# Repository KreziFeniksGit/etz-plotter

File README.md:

# ETZ plotter v2: whole device

**Open in FreeCAD:** `out/ETZ_plotter_parked.FCStd` (native, coloured, grouped) or `out/ETZ_plotter_parked.step`.
`ETZ_plotter_working.*` is the same model at Y 250, X 400, magnet face 5 mm, wrist 90 deg.
Tree: ETZ_plotter > Base_and_Y_axis, Y_carriage_and_X_axis, Wrist_module, Electronics_and_controls, Cables_and_chains, Fasteners, Field_reference.
Coordinates: X along the 600 mm side of the polygon, Y along the 500 mm side, Z up from the table (mm).

**Print files:** `out/printed/` has all 24 printed designs (15 frame parts + 9 wrist module parts) in print orientation, as STEP (PrusaSlicer, OrcaSlicer, Bambu Studio and Cura 5.x open STEP).
`y_beam_riser_x4` is printed four times.

**Wiring:** `wiring.md` (power, stop button, ESP32-S3 pins, every harness, driver currents).

**Tolerance tests:** `tolerance/` has 11 test coupons (STEP) and `tolerance/README.md` says how to test each one and which
constant to change. Print them before the real parts.

## Plywood, bolts and feet (v2.14)
- **Plywood DXF:** `out/plywood_base.dxf` (1:1, mm, origin = the board's -x/-y corner, seen from the top): outline + 18 through
  holes only (the shop cannot do depths). Hole list: `out/plywood_base_holes.csv`. Feet sit flat under the board; beam bolts M5x22.
- No wood screws: bolts through the plywood with a washer and hex nut underneath. Printed PETG feet (`foot_x4`) with an insert.
- The control board, panel, breadboard and battery are not in the model: place and drill them where you want.
- Control PCB: `pcb/README.md`.

## Stack-height sensor (v2.11)
- **TOF400C (VL53L1X)** under the wrist shelf at x 125.5, looking down, on 2 posts with M2 self-tapping screws.

## Camera (v2.16)
- **DF-1901A** board (54 x 19, lens d 14 x 23 in the middle, 3 M3 holes) sits ON TOP of the wrist shelf at x 150,
  along y, lens down through a 15 mm hole, on 3 nylon spacers 4.2x7x3 with 3x M3x12 + nut. Under the shelf the long lens
  would hit a 5-stack; on top its lowest point is 30 mm at face height 5. The single hole sits on a shelf tab at y -18..-3.
  It counts the checkers in a stack, reading with the magnet up (49..74 mm). Wiring and firmware notes: `wiring.md`.
  (An RDS3235 servo was tried and dropped, 16 Oct: the wrist stays on the MG996R.)

## Assembly simulation and 6 mm plywood (v2.9)
`tools/assembly_sim.py` builds the device in order (`docs/print_test_order.md`, "Order that matters") and checks that every
part can slide into place, every screw head can get in, a hex key or screwdriver reaches it, nuts can be held, T-nut slots are
still open and the soldering iron reaches every insert (`out/assembly_sim.json`: 0 problems). It found six places a person
could not assemble, now fixed:
- **Y carriage:** the 4 block screw heads were partly under the post socket walls: vertical notches through the walls (y walls 6 mm).
- **X motor mount:** two motor screw heads hit the cheeks: grooves in the cheeks.
- **Wrist carriage:** two block screw heads were under the servo plate: a notch for one; the other hole is dropped (3 screws on the X block).
- **Servo tabs:** the nylocs could not be held (servo case, boom): M2x8 self-tapping screws into the servo plate instead.
- **Magnet:** its screw head could not pass the 5 mm shaft bore: an M3x8 set screw in a Ruthex insert in the hub, magnet spun on (Loctite 243).
- **Control panel:** no room for a driver at the connector board screws: two 6 x 6 access windows in the +x wall.
**6 mm plywood** (Egor's board): 20 x 10 rubber feet in 1 mm recesses keep the plywood top at z 15, so nothing above moved;
beam bolt heads sunk 2 mm; all wood screws shortened so they bite 4..6 mm and none comes out underneath.

## V-slot frame and NEMA17 pancake wrist (v2.8)
- **2020 V-slot** everywhere (Y beam 400, post 130, boom 270): OpenBuilds section, 6 mm slot opening with the V-groove. The drop-in
  T-nuts, beam riser tongues, rails, socket and Soberizavod slot-6 cast brackets (T01) all still fit; the fastener check passes.
- **Wrist stepper = NEMA17 pancake 17HS4023S** (42 x 42 x 23, 0.7 A, ~13 N cm, 0.14 kg), on 4x M3x8 from under the shelf.
  To clear the lower arm and the end plate, the magnet axis moved +5 mm in X (to 110 from the servo axis) and -2.5 mm in Y,
  so **X travel is now pivot X 287..430** (the magnet still reaches X 397..540). The camera moved to x 147 and screws on from below.
  Picture: `out/render_wrist_nema17_pancake.png`.
- Servo lift: 0.23 N m needed with the heavier motor = 21 % of the MG996R's stall torque at 6 V.

## Stiffness, backlash and open belts (v2.7)
`docs/stiffness_review.md` has the whole review. FEA of the load-carrying printed parts (`tools/fea.py` -> `out/fea.json`,
gmsh + CalculiX from FreeCAD): every part now moves its pulley or idler <= 0.04 mm and tilts it <= 0.11 deg under 50 N of belt pull.
- **x_motor_mount:** 6 mm plate, top and bottom flanges, each arm also bolted (M5) to the post's -x face: pulley tilt 0.20 -> 0.025 deg.
- **y_motor_mount:** 6 mm plate, base on both sides, 4 gussets, 4 fixed wood screws (no tension slots any more).
- **x_idler_bracket** (the weakest part, 0.65 deg tilt -> 0.11): 12 mm end cap, a channel round an `x_idler_slider` pushed by an M3 screw in line with the axle.
- **y_idler_bracket:** axle slot + `y_idler_slider` pushed by an M3 screw in a lug (3 mm travel).
- **Open belts:** both ends clamp on the carriage (Y clamp 30 mm long with 3 screws, X clamp 42 mm with 3 screws), 6-9 teeth per end.
  Tension is set at the idler sliders; the motors never move.
- Backlash budget: 0.11 mm (Y) and 0.07 mm (X) on reversal (belt stretch, stepper, mounts, tooth clearance) against the 10 mm tolerance.
- Print the load parts with 6 walls and >= 50 % infill.

## Fasteners (v2.2)
All 140 fasteners are in the model (`Fasteners` in the tree): every screw with its head, nut, washer, heat-set insert or T-nut,
341 solids. `out/fastener_bom.csv` is the complete list with quantities. The check (`assembly.py`) found and fixed these:
- **Rubber feet:** a 3 mm foot cannot hold a screw. Now screw-on feet 20 x 7 mm sit 4 mm deep in pockets under the plywood
  (20 mm Forstner bit) and stick out 3 mm, so nothing else moves. Wood screw 3.5x12 from below.
- **Y beam bolts:** a flush M5 countersunk screw was either too short for the T-nut or hit the profile core. Now M5x20 socket caps
  in 9.3 mm counterbores, 7.5 deep, from below.
- **Y idler moved to y 12** (was 22): its axle nut hit the Y block when parked. The beam end plate of the idler bracket is lower
  (z 41.5) to clear the same nut.
- **X idler axle:** the nut would have hit the boom, so the bolt head now sits between the boom and the idler and the nut is outside.
- **Corner brackets:** the centre rib was in the way of the screw heads; modelled with side walls and holes 11 mm from the corner
  (VERIFY on your brackets). The two heads on one bracket touched at 10 mm.
- **Rails:** MGN12 rails now have their counterbored M3 holes (25 mm pitch; VERIFY), M3x8 into T-nuts.
- **Servo tab nuts:** the wrist carriage ribs were cut to 7 mm so the washers and nylocs fit.
- **Trays:** screw heads hit the breadboard and battery tray walls; ears moved out 2.5 / 1.5 mm, the breadboard 2 mm further +Y.
- **Y chain moving end:** button heads (M3x20) so the cable bundle fits over them.
Results: no fastener clips any part at rest or in 16 poses against the moving parts; every screw engages enough
(inserts >= 4 mm, T-nuts >= 2.5..3 mm, nuts fully, tapped metal within its thread depth) and blind screws end inside their target.

## Cable chains and cables (v2.1)
- **X chain** (10 x 15 R18, 297.5 mm = 17 links since v2.17, was 280): fixed end on the boom top at x 230..250 (2 M3 drop-in T-nuts), lower run lies on the boom,
  U-bend toward +X, upper run back to the moving end on top of `chain_post`. The post top is now at z 208 (boom top 172 + 2 x R18)
  and has a 45 deg brace and a slot for the end link screws (any hole spacing fits).
- **Y chain** (10 x 15 R18, 250 mm): lower run in the printed `y_chain_guide` on the plywood (x 235.5, y 213..421), U-bend toward +Y,
  upper run to the moving end on top of the Y carriage (M3 + nut through a slot). The guide's 17 mm floor (pockets underneath)
  lifts the chain so the upper run meets the carriage top.
- Both chains are rebuilt for every pose: the bend sits where the chain length puts it (it moves at half the carriage speed).
  X bend x 401..484 (v2.17), Y bend y 250..418: the Y bend stays 57 mm inside the polygon edge.
- **Cable tunnel:** the Y beam now sits on four printed risers (10 mm), so the cables from the battery, the panel and the Y motor
  cross under the beam (at y 60 and y 205) to the electronics board. Before this, nothing could reach the board without crossing the
  Y carriage's path. The post is 10 mm shorter (130 mm), so the boom height is unchanged.
- The cable bundles are modelled as tubes (`cable_*`), so the collision check sees them.
- **X travel was pivot X 292..435** (v2.2; 287..430 since v2.8; **287..452 since v2.17**, see below) (magnet X 397..540, the cells need 397..537). Raising the Y axis left the
  wrist carriage 3 mm into the Y carriage at the old minimum (256).

## Whole-device check (`assembly.py`, results in `out/assembly_review.json`)
- no clash between any two parts at rest, and no cable passes through a part;
- no collision in 54 poses: Y 40/124/208/292/376 x X 287/328/369.5/411/452 x face height 5/40 mm, plus wrist +-90/180, chains and cables included;
- parked device inside the 600 x 500 polygon and zones 1+2, feet only in zone 1; during the run parts may leave the polygon (ETZ rules): at PXB 452 the wrist shelf passes 7 mm beyond the 600 mm edge;
- lowest part over the field at face height 5 mm: camera lens at 30 mm (clears a 5-stack);
- every printed part: walls >= 2.4 mm, no unrounded internal corner, no overhang > 45 deg, widest bridge 9.3 mm, fits 220 x 220.

## Stability and stiffness (`tools/stability.py`, results in `out/stability.json`)
- Mass about 4.1 kg with all screws (base 2.61, Y carriage and boom 1.03, wrist module 0.42, chains 0.08; v2.7).
- Tipping: the centre of mass stays at least 92 mm inside the feet. Tipping would need 31 m/s2 (3.2 g); the design acceleration is 2 m/s2.
- Rail loads: worst moment 1.65 N m on the Y block against 37.5 N m rated (23x margin).
- Sag of the magnet from the aluminium profiles: at most 0.16 mm. The printed socket and the corner brackets add more; calibration takes it out,
  and the placement tolerance is 10 mm.

**Regenerate:** `freecad export_gui.py` (needs the FreeCAD GUI for colours), `./fcpy assembly.py` and `./fcpy tools/stability.py`
with FreeCAD's python. `./fcpy tools/render_pose.py Y X h wrist out.png` renders any pose.

**Frame parts (same rules as the wrist module):** y_carriage (post socket with round relief groove, block screws sunk 5 mm: fit them
before the post; slot for the Y chain end), y_belt_spacer, y_belt_clamp (two belt ends, tooth grooves), y_motor_mount (fixed, gusseted), y_idler_bracket
(idler slot, tension lug, Y home switch post), y_idler_slider, y_beam_riser x4 (tongues locate the beam in its slot), y_chain_guide, x_motor_mount (M5 into the post's +y and -x faces,
X home switch), x_idler_bracket (slotted axle, tension lug), x_idler_slider, post_cap, foot_x4. The control panel and the battery / breadboard trays are no longer printed
(v2.14: Egor places the electronics on the plywood by hand).

**Screws:** `out/fastener_bom.csv` is the complete list (it replaces the screw lists further down where they differ). Zip ties are not modelled.

---

# ETZ plotter v2: component choices and the wrist module

Model v2 follows the design rules: parameters at the top of the script, separate printable parts, rule tolerances, 2.4 mm minimum walls, filleted corners, at most 45 degree overhangs, short bridges, cable-tie features. The CAD is FreeCAD (OpenCascade) Python, so the solids are real B-rep with true fillets.

## Files
- `wrist/wrist_module.py`: the parametric model (all dimensions in sections 1 to 3 at the top).
- `wrist/review.py`: the review that produced the numbers below.
- `wrist/out/*.step`: the wrist parts in print orientation (the same files are in `out/printed/`). `wrist/out/wrist_module_assembly.step`: the whole module with the bought parts.
- `wrist/out/review.json`: all review results. `wrist/out/*.png`: renders.
- `components.csv`: every component of the device, with the reason it was chosen and the data used in the CAD.
- `vendor/`: real models of bought parts (MG996R, 25T aluminium arm horn, 17HS16-2004S1; 11HS12-0674S is no longer used; no model of the 17HS4023S pancake yet; the 684 bearing and MGN12 meshes are kept for reference only). The exported STEP/FCStd use them; the fast checks use simple shapes sized from them, and `assembly.py` also re-checks with the real models (`detailed_*` results).

Run the model yourself: install FreeCAD 1.0 or 1.1 (Linux AppImage or Windows installer), then
`freecadcmd -c "exec(open('wrist_module.py').read())"`, or open the file in the FreeCAD GUI with Macro > Macros > Execute.

## Wrist module: design decisions
- **Carriage and servo plate are one L-part.** This gives a stiff joint with no screws. It prints with the block face down; the servo window has a W-shaped 45 degree roof, so it needs no bridge. The lower pivot boss is a teardrop for the same reason.
- **Parallelogram, 80 mm arms.** The magnet face stays level from 5 to 40 mm. The servo swings +-12.6 degrees and the X shift (up to 1.9 mm) is corrected in software.
- **Bearings in the arms, clamped on the inner ring only.** A nylon spacer 4.2 x 7 x 3 goes through a 7.6 mm shoulder hole on one side and a 7 mm shim washer goes on the other, so nothing touches the outer ring. Moving gaps are 0.5 to 0.8 mm.
- **The top arm bolts to a 25T aluminium single-arm horn**: centre screw into the spline plus one M3 into the horn's tapped hole at r 24, with the horn's arm lying along the top arm.
- **Lightening slots** in both arms remove about 25 % of the web. The two flanges carry the bending, so stiffness hardly drops.
- **Shelf and end plate are separate flat parts.** Both print flat, so the stepper and pivot holes are vertical, round and accurate. They join with two M3 screws into inserts in the end plate's foot pad, which sits clear of the pivot nut.
- **The belt clamp** has half-round grooves at 2 mm pitch that take the belt teeth; it holds both ends of the open X belt (42 mm, 3 screws).
- **No wrist home sensor** (Egor, 12 Oct): the hall switch and the hub's flag magnet were removed. Set the wrist to its mark by hand before power-up; the firmware counts the angle from there.
- **MG996R servo**: M2 bolts with large washers through its 4.5 mm tab holes (M3 would leave only 2 mm of plastic to the window); shallow grooves take the ribs under its tabs.

## Tolerances used
| Feature | Size |
|---|---|
| M3 / M4 clearance holes | 3.25 / 4.25 (+0.25); camera M2 self-tapping pilots 1.8 |
| Wrist NEMA17 pancake screw holes, pilot | 3.2, 22.2 (+0.2) |
| 684ZZ press seat | 9.12 (+0.12) |
| D-bore on the stepper shaft | 5.12 with flat at 4.62 (+0.12) |
| Servo window | case +0.4 per side |
| Spacer in the shoulder hole | 0.3 radial |
| Heat-set insert hole | 4.0 x 6.5 deep |

## Review results
- Interference: none, checked at face height 5, 10, 16, 22.5, 30, 36 and 40 mm and wrist angle 0, 90 and 180 degrees, with every bought part included.
- Smallest moving gaps: 0.3 mm (spacers in the arms) and 0.5 mm (lower arm to its boss and to the shelf). Servo case to window: 0.36 mm.
- Lowest point at face height 5 mm: camera lens 30 mm, which clears a stack of 5 checkers (25 mm).
- Every printed part: walls at least 2.4 mm, no unrounded internal corner, no overhang beyond 45 degrees, widest bridge 6.3 mm, all fit a 220 x 220 bed. About 72 g of PETG.

## Wrist module parts list
| Part | Qty | Print orientation |
|---|---|---|
| wrist_carriage | 1 | block face down |
| x_belt_riser | 1 | standing |
| x_belt_clamp | 1 | grooves up |
| chain_post | 1 | on its -Y face |
| arm_top, arm_bottom | 1 + 1 | flat |
| end_plate | 1 | -Y face down |
| shelf | 1 | stepper face down |
| wrist_hub | 1 | shaft end down |

Suggested settings: PETG, 0.2 mm layers, 4 walls, 40 % gyroid, no supports.

**Bought parts:** MG996R servo + 25T aluminium arm horn, NEMA17 pancake 17HS4023S, P20/15 5 V magnet, 3x 684ZZ, 6x nylon spacer 4.2x7x3 (3 pivots, 3 camera), 3x shim 4.2x7x0.8, camera DF-1901A, 10x Ruthex M3x5.7.

**Screws:**
- 4x M3x6 ISO4762: carriage to the rail block.
- 4x M2x12 ISO4762 + DIN 9021 washer under the head + nyloc (no washer under the nut): servo tabs.
- 1x M4x30 ISO4762 + nyloc: lower A pivot.
- 2x M4x20 ISO4762 + washer + nyloc: B pivots.
- 2x M3x10: belt riser. 2x M3x10: chain post. 2x M3x8: belt clamp. 2x M3x12 + nut: X chain end on the post.
- 2x M3x10: shelf to end plate.
- 4x M3x8 ISO7380: wrist NEMA17 pancake, from below the shelf.
- 3x M3x12 ISO4762 + hex nut: camera board, from the top through the board, a nylon spacer and the shelf, nut below.
- 1x M3x6 or M3x8 ISO7380: magnet. Use the length that suits the magnet's thread depth.
- 1x M3x10 ISO7380: top arm to the horn (r 24 hole, tapped M3 in the horn: VERIFY).

## Assembly order
1. Press the heat-set inserts: riser (2 top, 2 bottom), chain post foot (2), end plate foot (2).
2. Screw the wrist carriage to the rail block (4x M3x6 from below). Do this before the servo goes in: the servo covers two of the screws.
3. Fit the riser and chain post from below (M3x10).
4. Push the servo through the window from the -Y side and bolt the tabs (M2x12, large washer under the head, nyloc).
5. Press the bearings into both arms from the end-plate side (flush).
6. Set the servo to its centre pulse (1500 us), fit the horn with the arm level, and screw the top arm to it.
7. Lower pivot A: M4x30 from the servo side, through the boss, spacer, bearing, shim and nyloc. Snug only: the arm must swing freely.
8. Screw the shelf to the end plate (2x M3x10 from below). Mount the NEMA17 pancake (4x M3x8 from below, connector toward +x, away from the end plate) and the camera on top (3x M3x12 down through board + spacer + shelf, nuts below).
9. B pivots: M4x20 with washer and spacer from the arm side, then bearing, shim, end plate and nyloc.
10. Press the hub onto the stepper shaft (D flat aligned), with the magnet screw already inside it, then screw on the electromagnet.
11. Route the cables (see wiring.md): the harness tie on the end plate, two ties round the top arm, servo lead to the bundle, two ties on the chain post.

## Measure before printing (marked VERIFY in the script)
Wrist stepper 17HS4023S: body height (23), shaft length (20..24; the hub takes up to 23), screw thread depth (4.5), which side the connector is on. Servo (MG996R, taken from a third-party STEP model): tab face to cover top, case height, spline centre to case end, tab hole spacing (48.4), horn face height, horn screw hole thread. Magnet: thread depth. Enter the measured values at the top of `wrist_module.py`; everything else follows.

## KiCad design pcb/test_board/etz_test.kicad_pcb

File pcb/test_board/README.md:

# ETZ control: TEST BOARD T1 (2-layer, JLCPCB), 9 Nov 2026

This is a test version of `../etz_control.kicad_sch`, built as a factory 2-layer board. **The originals are untouched.** Everything lives in this folder.

> **Do not order T1 yet (pin audit, 10 Nov 2026).** `etz_control.kicad_sch` still has the *old* single-board pin map (22 Oct). The split boards and firmware v5 use the new one (`wiring.md` section 2, `firmware/include/pins.h`). On T1 every STEP/DIR pin, the TMC UART (15/16 instead of 5/6), I2C, the home switches, start, the LED, the magnet and the servo are on different GPIOs. Driver EN sits on GPIO13 with a pull-up, so the drivers stay off. The UART addresses are 0/1/2/3 instead of X 0, Y 2, wrist 3. Next step: rebuild T1 with the `pins.h` map.

| File | What it is |
|---|---|
| `test_parts.py` | Parts table: a copy of the one in `build_pcb.py`, plus the fixes below |
| `test_sch.py` → `etz_test.kicad_sch`, `etz_test_schematic.pdf` | The fixed schematic (ERC 0, netlist identical to the parts table) |
| `layout.py` → `etz_test.kicad_pcb` | The board, made from the schematic's netlist; footprints are linked to the symbols, so "Update PCB from Schematic" works |
| `nl.py`, `probe.py` | Netlist reader and a footprint-size helper |
| `renders/` | Top and bottom pictures |

To rebuild:
```
"C:\Program Files\KiCad\10.0\bin\python.exe" test_sch.py
"C:\Program Files\KiCad\10.0\bin\python.exe" layout.py 30
```

## Fixes compared to etz_control v1.0, and why

1. **XT30 polarity (J11).** The KiCad AMASS footprint has pad 1 = minus and pad 2 = plus. v1.0 had them swapped, so the drive battery would have reversed VM on all four TMC2209s, which kills them.
2. **TVS diodes D3 and D4 (SMBJ18A) at both power inputs.** They clamp spikes when a plug goes in and when motors brake. 4S LiPo is 16.8 V max, so an 18 V stand-off does not conduct in normal use. If the battery is plugged in backwards, the TVS shorts it and the battery fuse blows, and nothing else gets reverse voltage. VERIFY: the clamp is ~29 V and the TMC2209 VM absolute maximum is 29 V, which leaves no margin. SMBJ16A (clamp ~26 V) is the safer choice if 4S never goes above 16.8 V (stand-off 16 V, so it leaks a little at full charge).
3. **100 nF ceramic C9–C12 at every driver VM pin.** The 100 µF electrolytic is too slow for the chopper's fast current edges. The small cap sits on the VM and GND pins.
4. **4.7 µF ceramic C13 and C14 at each Mini560 input.** A buck draws its input current in sharp pulses. A ceramic cap right at the input keeps that loop small, which means less noise.
5. **ADC filter caps C15 (VBAT_SENSE) and C16 (STOP_SENSE),** like C8 already does on A_IO. A divider with a cap gives the ADC a low-impedance source.
6. **Test points TP5 VBAT, TP6 VDRIVE, TP7 GND,** so the meter probe has a place to go.

## Layout decisions

- **Zones:** power on the right edge (XT60 + XT30 face out, TVS on their pins, then both bucks). Drivers along the top, each with its motor plug straight above its motor pins. ESP32 bottom-left with the USB end at the left edge. All small plugs along the bottom.
- **Drivers in pin order:** W, Y, X, spare left to right, which is the order of their STEP/DIR pins on the ESP32. Signals run straight down with no crossings.
- **Power first:** VBAT, VDRIVE, the 5 V rails, the motor phases and 3V3 are routed first, at widths chosen by current (1.5 / 1.0 / 0.8 / 0.5 mm). Signals are routed afterwards, around them.
- **Ground:** no ground traces. Every SMD ground pad gets its own via into the pours. Both layers are GND pours, tied with stitching vias. The bottom layer is kept as clean as possible so the return currents have a solid path.
- **Labels:** each plug's name is on the silkscreen (X, Y, TOF, PANEL...), with + and − at the battery plugs. The revision is also etched in copper, so a bare board can still be identified.

## Left open (VERIFY / next revision)

- **GPIO38 (TOF_XSHUT).** On DevKitC-1 v1.1 the RGB LED is on IO38, and nothing can be moved: every allowed GPIO is already in use, and 3, 45, 46 and 48 are forbidden by the README. It works on v1.0. On v1.1 the LED will flicker with XSHUT. Check which DevKit version is in the box.
- **No ESD protection on J17 (panel cable).** It goes off-board, so it is the most likely place for a zap. Next revision: a TVS array.
- **No 22 Ω series resistors on the STEP lines.** They would soften edge ringing on long traces. Not needed at these lengths.
- **The spare driver U7 has no STEP/DIR.** All GPIOs are used. It only gets its power, plug and UART address.
- **Reverse polarity is handled by TVS + fuse (crowbar).** A P-FET would be nicer (no blown fuse), but at 4S the gate needs a zener clamp. See pcb-brain "P-MOSFET power path".

## Checks run (10 Nov 2026)

- Schematic: ERC 0. The netlist is identical to the parts table (77 parts, 58 nets).
- Board 146 x 100 mm, 2 layers. 580 tracks + vias, 25 ground vias at SMD pads, 193 stitching vias.
- DRC (`kicad-cli pcb drc --schematic-parity`): **0 errors, 0 unconnected, 0 schematic-parity issues**. One silkscreen-overlap warning (C13 reference touches the XT60 outline; cosmetic).
- Power width: the routes have their class width. Short neck-downs happen only where a track enters 2.54 mm-pitch module pins. The longest is about 10 mm at 1.125 mm, still ~3 A (VERIFY against the real current draw).
- 5 GND header pins (J9.2, U1.23, U3.3, U3.16, U4.16) had their thermal spokes blocked by passing tracks, so they connect solid to the pour. These are 0.64 mm pins, still easy to solder.
- Teardrops: the KiCad 10 Python API didn't expose them. Add them in the GUI if you want (Edit → Edit Teardrops).
- `gerbers/` contains the Gerber + drill files for JLCPCB. **Before ordering, open the board in KiCad, look it over yourself, and zip the gerbers.**

## How the routing works (lessons used)

1. Pass 1: only power, motor and 3V3 nets are visible to Freerouting. They get the best paths and the widest tracks.
2. The power tracks are locked. Pass 2 routes signals around them.
3. GND is never routed as tracks. Each SMD ground pad has its own via, and both layers are GND pour.
4. Bug found and fixed: at first the vias were netless, and Freerouting took them for other nets (shorts to GND). Giving them GND from the start stopped that.

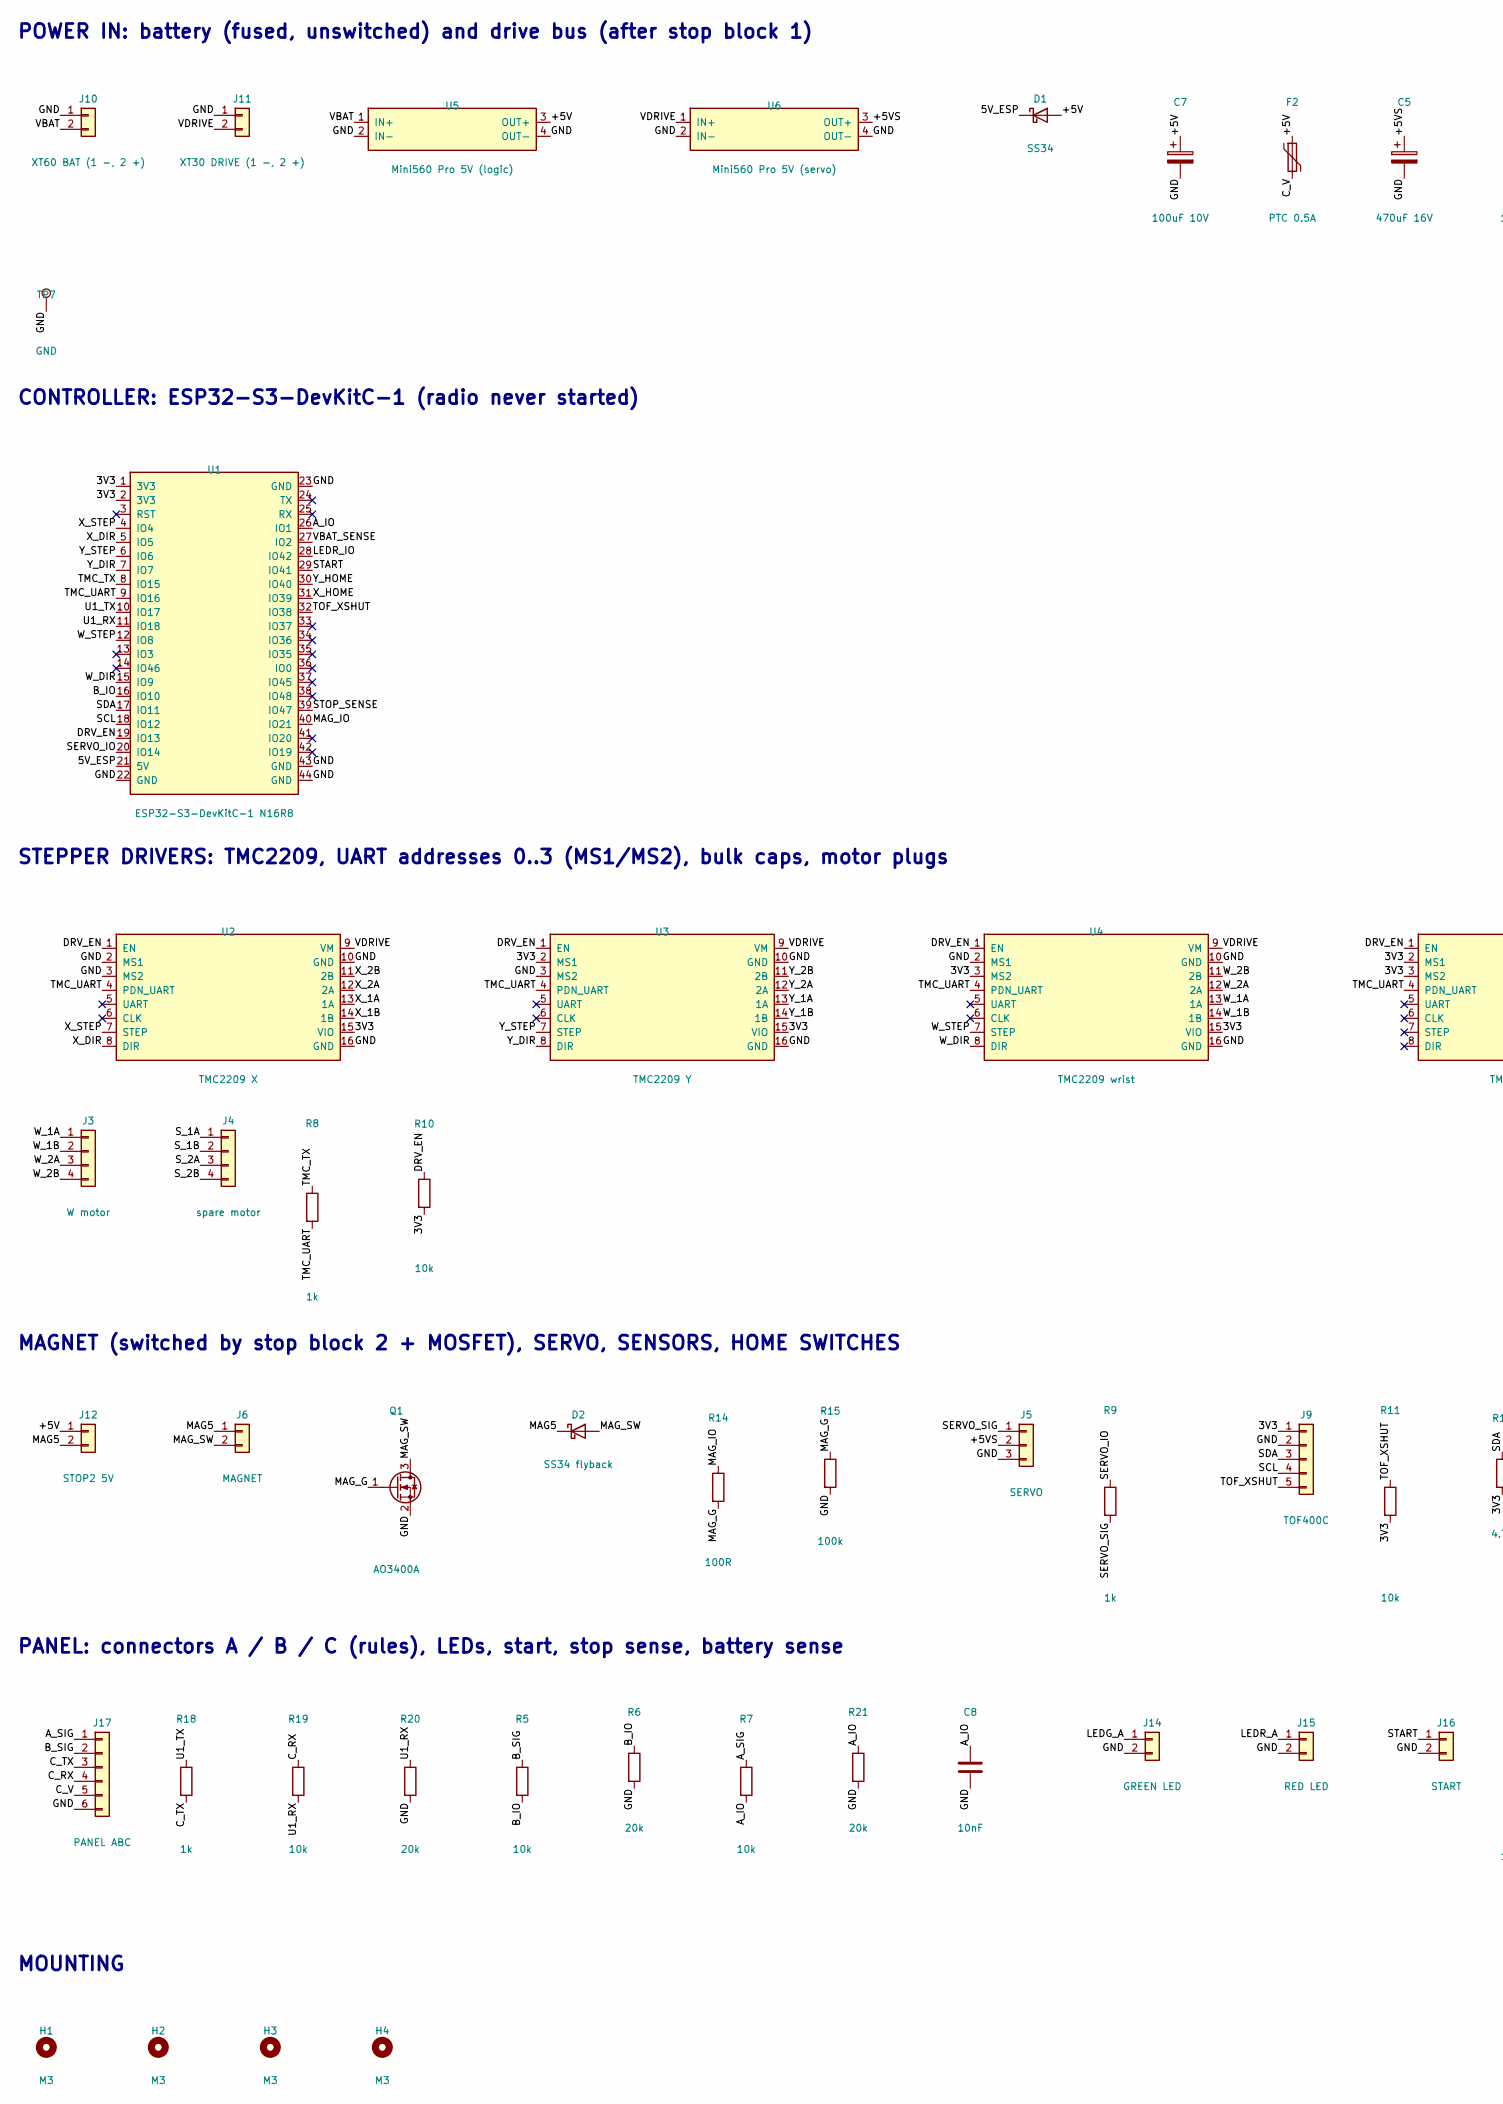
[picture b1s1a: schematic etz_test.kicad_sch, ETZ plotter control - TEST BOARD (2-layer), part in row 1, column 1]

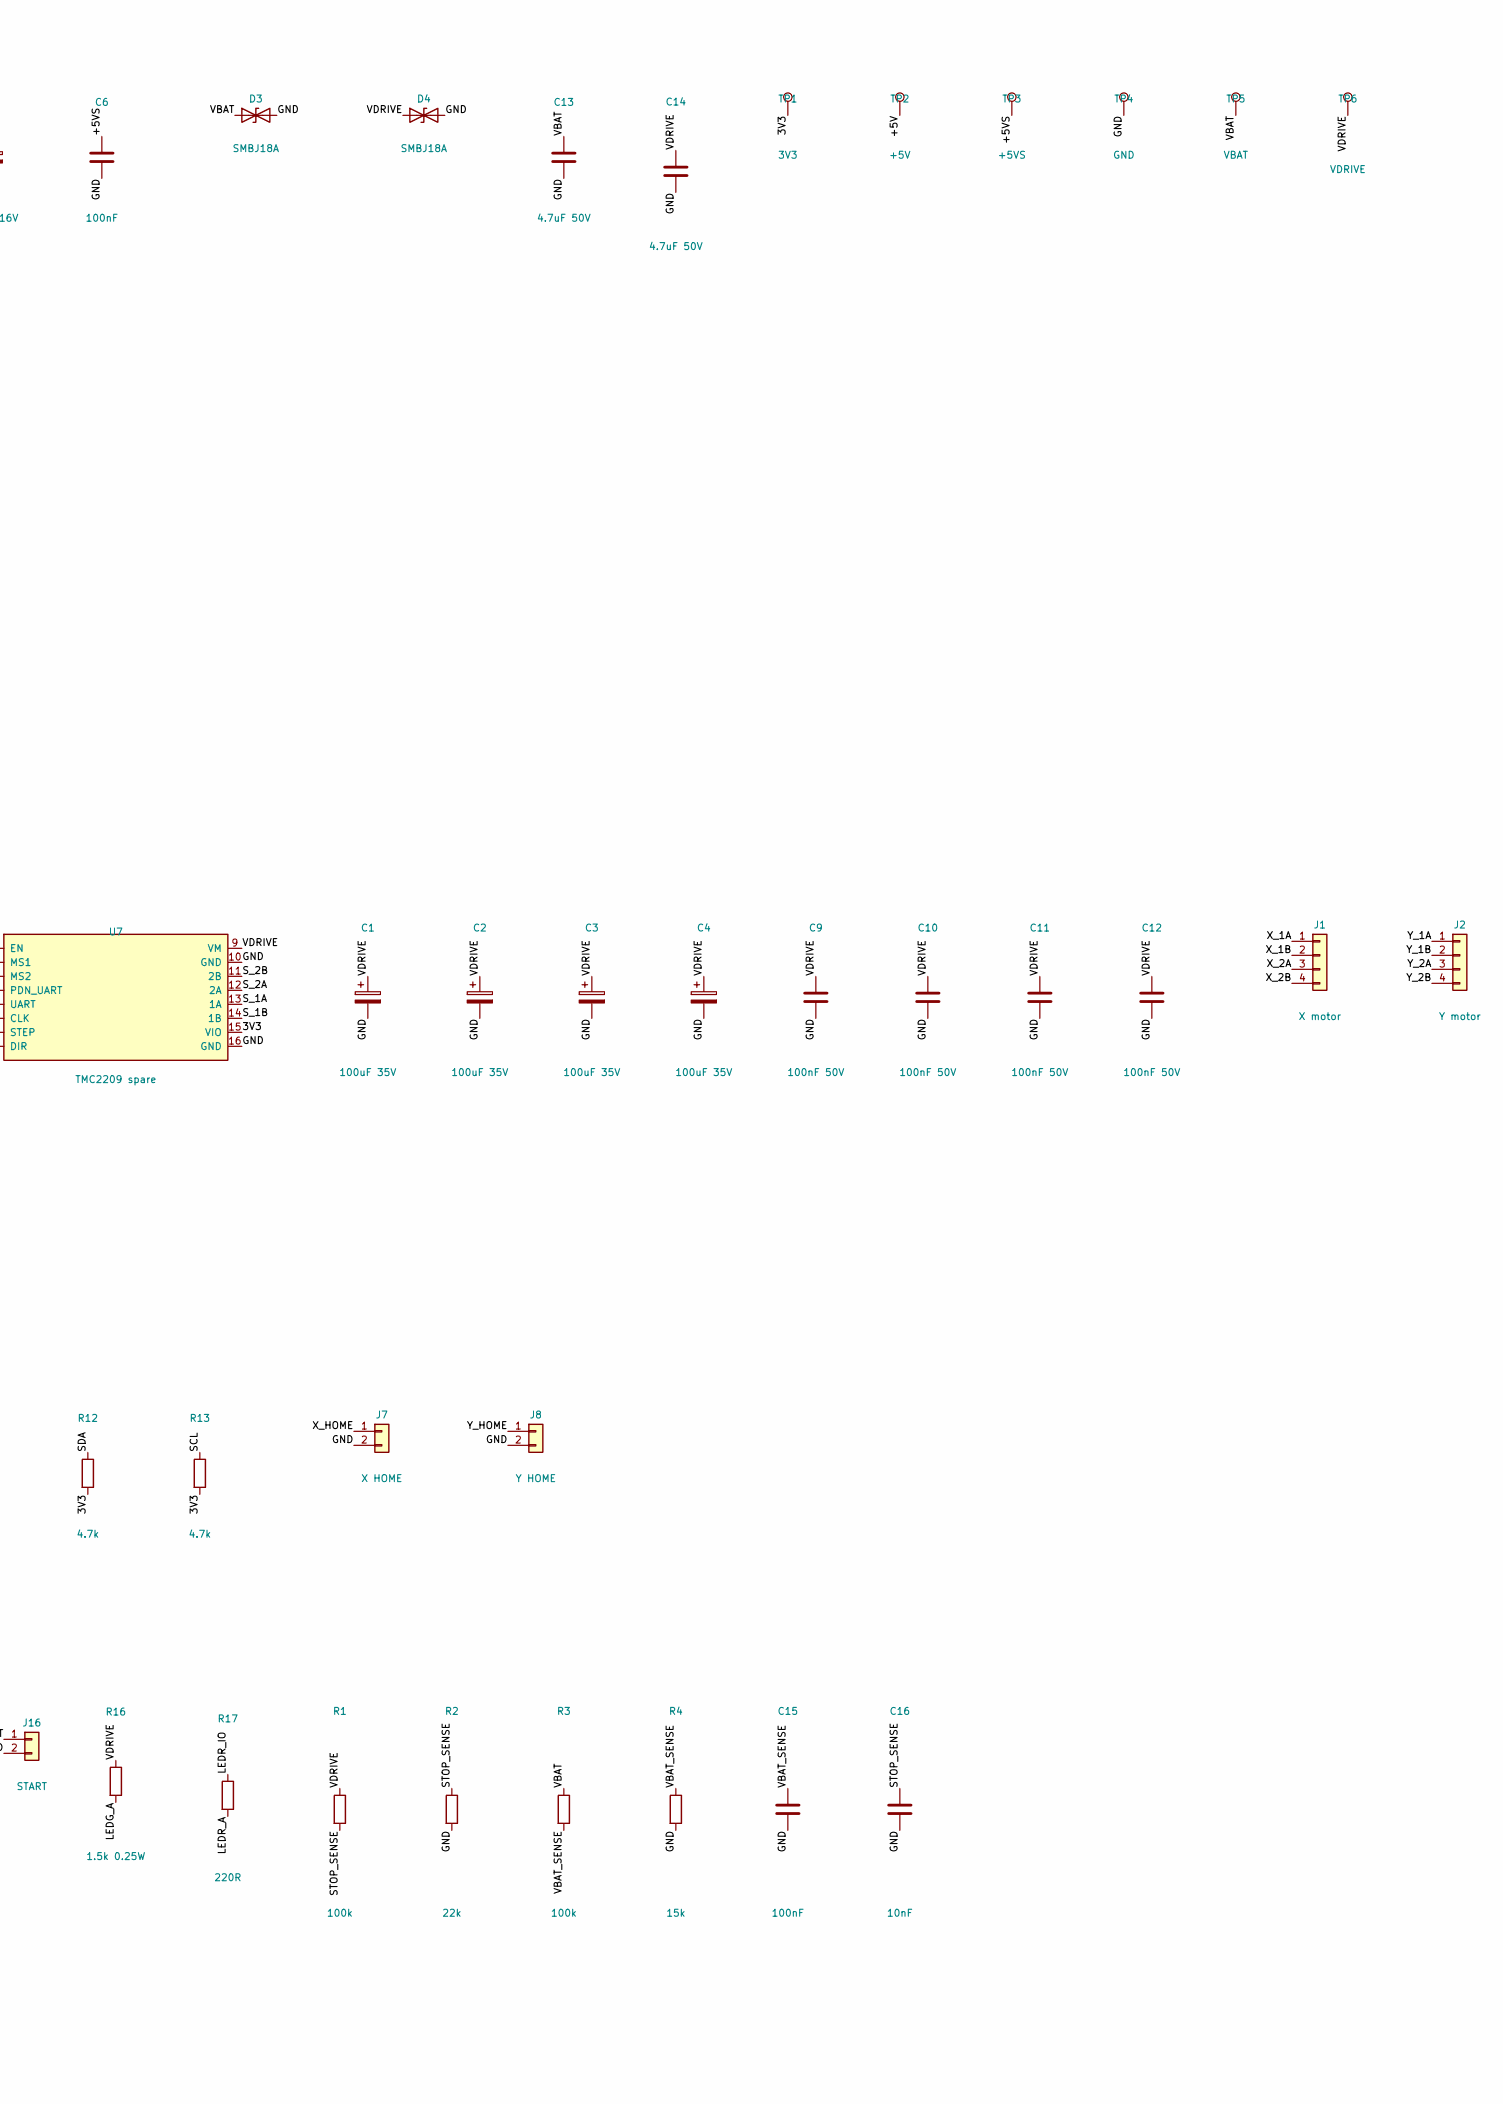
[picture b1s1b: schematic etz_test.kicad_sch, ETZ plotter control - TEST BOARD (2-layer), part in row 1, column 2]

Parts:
C1, C2, C3, C4: 100uF 35V; CP_Elec_8x10
C5: 470uF 16V; CP_Elec_8x10
C6, C15: 100nF; C_0805_2012Metric_Pad1.18x1.45mm_HandSolder
C7: 100uF 10V; CP_Elec_6.3x7.7
C8, C16: 10nF; C_0805_2012Metric_Pad1.18x1.45mm_HandSolder
C9, C10, C11, C12: 100nF 50V; C_1206_3216Metric_Pad1.33x1.80mm_HandSolder
C13, C14: 4.7uF 50V; C_1206_3216Metric_Pad1.33x1.80mm_HandSolder
D1: SS34; D_SMA_Handsoldering
D2: SS34 flyback; D_SMA_Handsoldering
D3, D4: SMBJ18A; D_SMB_Handsoldering
F2: PTC 0.5A; Fuse_1206_3216Metric_Pad1.42x1.75mm_HandSolder
H1, H2, H3, H4: M3; MountingHole_3.2mm_M3
J1: X motor; JST_XH_B4B-XH-A_1x04_P2.50mm_Vertical
J2: Y motor; JST_XH_B4B-XH-A_1x04_P2.50mm_Vertical
J3: W motor; JST_XH_B4B-XH-A_1x04_P2.50mm_Vertical
J4: spare motor; JST_XH_B4B-XH-A_1x04_P2.50mm_Vertical
J5: SERVO; PinHeader_1x03_P2.54mm_Vertical
J6: MAGNET; JST_XH_B2B-XH-A_1x02_P2.50mm_Vertical
J7: X HOME; JST_XH_B2B-XH-A_1x02_P2.50mm_Vertical
J8: Y HOME; JST_XH_B2B-XH-A_1x02_P2.50mm_Vertical
J9: TOF400C; JST_XH_B5B-XH-A_1x05_P2.50mm_Vertical
J10: XT60 BAT (1 -, 2 +); AMASS_XT60PW-M_1x02_P7.20mm_Horizontal
J11: XT30 DRIVE (1 -, 2 +); AMASS_XT30PW-M_1x02_P2.50mm_Horizontal
J12: STOP2 5V; JST_XH_B2B-XH-A_1x02_P2.50mm_Vertical
J14: GREEN LED; JST_XH_B2B-XH-A_1x02_P2.50mm_Vertical
J15: RED LED; JST_XH_B2B-XH-A_1x02_P2.50mm_Vertical
J16: START; JST_XH_B2B-XH-A_1x02_P2.50mm_Vertical
J17: PANEL ABC; JST_XH_B6B-XH-A_1x06_P2.50mm_Vertical
Q1: AO3400A; SOT-23
R1, R3, R15: 100k; R_0805_2012Metric_Pad1.20x1.40mm_HandSolder
R2: 22k; R_0805_2012Metric_Pad1.20x1.40mm_HandSolder
R4: 15k; R_0805_2012Metric_Pad1.20x1.40mm_HandSolder
R5, R7, R10, R11, R19: 10k; R_0805_2012Metric_Pad1.20x1.40mm_HandSolder
R6, R20, R21: 20k; R_0805_2012Metric_Pad1.20x1.40mm_HandSolder
R8, R9, R18: 1k; R_0805_2012Metric_Pad1.20x1.40mm_HandSolder
R12, R13: 4.7k; R_0805_2012Metric_Pad1.20x1.40mm_HandSolder
R14: 100R; R_0805_2012Metric_Pad1.20x1.40mm_HandSolder
R16: 1.5k 0.25W; R_0805_2012Metric_Pad1.20x1.40mm_HandSolder
R17: 220R; R_0805_2012Metric_Pad1.20x1.40mm_HandSolder
TP1: 3V3; TestPoint_THTPad_D2.0mm_Drill1.0mm
TP2: +5V; TestPoint_THTPad_D2.0mm_Drill1.0mm
TP3: +5VS; TestPoint_THTPad_D2.0mm_Drill1.0mm
TP4, TP7: GND; TestPoint_THTPad_D2.0mm_Drill1.0mm
TP5: VBAT; TestPoint_THTPad_D2.0mm_Drill1.0mm
TP6: VDRIVE; TestPoint_THTPad_D2.0mm_Drill1.0mm
U1: ESP32-S3-DevKitC-1 N16R8; ESP32-S3-DevKitC-1
U2: TMC2209 X; TMC2209_Module
U3: TMC2209 Y; TMC2209_Module
U4: TMC2209 wrist; TMC2209_Module
U5: Mini560 Pro 5V (logic); Mini560_Pro
U6: Mini560 Pro 5V (servo); Mini560_Pro
U7: TMC2209 spare; TMC2209_Module

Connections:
/3V3: J9.1, R10.2, R11.2, R12.2, R13.2, TP1.1, U1.1 (3V3), U1.2 (3V3), U2.15 (VIO), U3.2 (MS1), U3.15 (VIO), U4.3 (MS2), U4.15 (VIO), U7.2 (MS1), U7.3 (MS2), U7.15 (VIO)
/5V_ESP: D1.1 (K), U1.21 (5V)
/+5V: C7.1, D1.2 (A), F2.1, J12.1, TP2.1, U5.3 (OUT+)
/+5VS: C5.1, C6.1, J5.2, TP3.1, U6.3 (OUT+)
/A_IO: C8.1, R7.2, R21.1, U1.26 (IO1)
/A_SIG: J17.1, R7.1
/B_IO: R5.2, R6.1, U1.16 (IO10)
/B_SIG: J17.2, R5.1
/C_RX: J17.4, R19.1
/C_TX: J17.3, R18.2
/C_V: F2.2, J17.5
/DRV_EN: R10.1, U1.19 (IO13), U2.1 (EN), U3.1 (EN), U4.1 (EN), U7.1 (EN)
/GND: C1.2, C2.2, C3.2, C4.2, C5.2, C6.2, C7.2, C8.2, C9.2, C10.2, C11.2, C12.2, C13.2, C14.2, C15.2, C16.2, D3.2 (A2), D4.2 (A2), J5.3, J7.2, J8.2, J9.2, J10.1, J11.1, J14.2, J15.2, J16.2, J17.6, Q1.2 (S), R2.2, R4.2, R6.2, R15.2, R20.2, R21.2, TP4.1, TP7.1, U1.22 (GND), U1.23 (GND), U1.43 (GND), U1.44 (GND), U2.2 (MS1), U2.3 (MS2), U2.10 (GND), U2.16 (GND), U3.3 (MS2), U3.10 (GND), U3.16 (GND), U4.2 (MS1), U4.10 (GND), U4.16 (GND), U5.2 (IN-), U5.4 (OUT-), U6.2 (IN-), U6.4 (OUT-), U7.10 (GND), U7.16 (GND)
/LEDG_A: J14.1, R16.2
/LEDR_A: J15.1, R17.2
/LEDR_IO: R17.1, U1.28 (IO42)
/MAG5: D2.1 (K), J6.1, J12.2
/MAG_G: Q1.1 (G), R14.2, R15.1
/MAG_IO: R14.1, U1.40 (IO21)
/MAG_SW: D2.2 (A), J6.2, Q1.3 (D)
/SCL: J9.4, R13.1, U1.18 (IO12)
/SDA: J9.3, R12.1, U1.17 (IO11)
/SERVO_IO: R9.1, U1.20 (IO14)
/SERVO_SIG: J5.1, R9.2
/START: J16.1, U1.29 (IO41)
/STOP_SENSE: C16.1, R1.2, R2.1, U1.39 (IO47)
/S_1A: J4.1, U7.13 (1A)
/S_1B: J4.2, U7.14 (1B)
/S_2A: J4.3, U7.12 (2A)
/S_2B: J4.4, U7.11 (2B)
/TMC_TX: R8.1, U1.8 (IO15)
/TMC_UART: R8.2, U1.9 (IO16), U2.4 (PDN_UART), U3.4 (PDN_UART), U4.4 (PDN_UART), U7.4 (PDN_UART)
/TOF_XSHUT: J9.5, R11.1, U1.32 (IO38)
/U1_RX: R19.2, R20.1, U1.11 (IO18)
/U1_TX: R18.1, U1.10 (IO17)
/VBAT: C13.1, D3.1 (A1), J10.2, R3.1, TP5.1, U5.1 (IN+)
/VBAT_SENSE: C15.1, R3.2, R4.1, U1.27 (IO2)
/VDRIVE: C1.1, C2.1, C3.1, C4.1, C9.1, C10.1, C11.1, C12.1, C14.1, D4.1 (A1), J11.2, R1.1, R16.1, TP6.1, U2.9 (VM), U3.9 (VM), U4.9 (VM), U6.1 (IN+), U7.9 (VM)
/W_1A: J3.1, U4.13 (1A)
/W_1B: J3.2, U4.14 (1B)
/W_2A: J3.3, U4.12 (2A)
/W_2B: J3.4, U4.11 (2B)
/W_DIR: U1.15 (IO9), U4.8 (DIR)
/W_STEP: U1.12 (IO8), U4.7 (STEP)
/X_1A: J1.1, U2.13 (1A)
/X_1B: J1.2, U2.14 (1B)
/X_2A: J1.3, U2.12 (2A)
/X_2B: J1.4, U2.11 (2B)
/X_DIR: U1.5 (IO5), U2.8 (DIR)
/X_HOME: J7.1, U1.31 (IO39)
/X_STEP: U1.4 (IO4), U2.7 (STEP)
/Y_1A: J2.1, U3.13 (1A)
/Y_1B: J2.2, U3.14 (1B)
/Y_2A: J2.3, U3.12 (2A)
/Y_2B: J2.4, U3.11 (2B)
/Y_DIR: U1.7 (IO7), U3.8 (DIR)
/Y_HOME: J8.1, U1.30 (IO40)
/Y_STEP: U1.6 (IO6), U3.7 (STEP)

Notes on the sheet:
POWER IN: battery (fused, unswitched) and drive bus (after stop block 1)
CONTROLLER: ESP32-S3-DevKitC-1 (radio never started)
STEPPER DRIVERS: TMC2209, UART addresses 0..3 (MS1/MS2), bulk caps, motor plugs
MAGNET (switched by stop block 2 + MOSFET), SERVO, SENSORS, HOME SWITCHES
PANEL: connectors A / B / C (rules), LEDs, start, stop sense, battery sense
MOUNTING

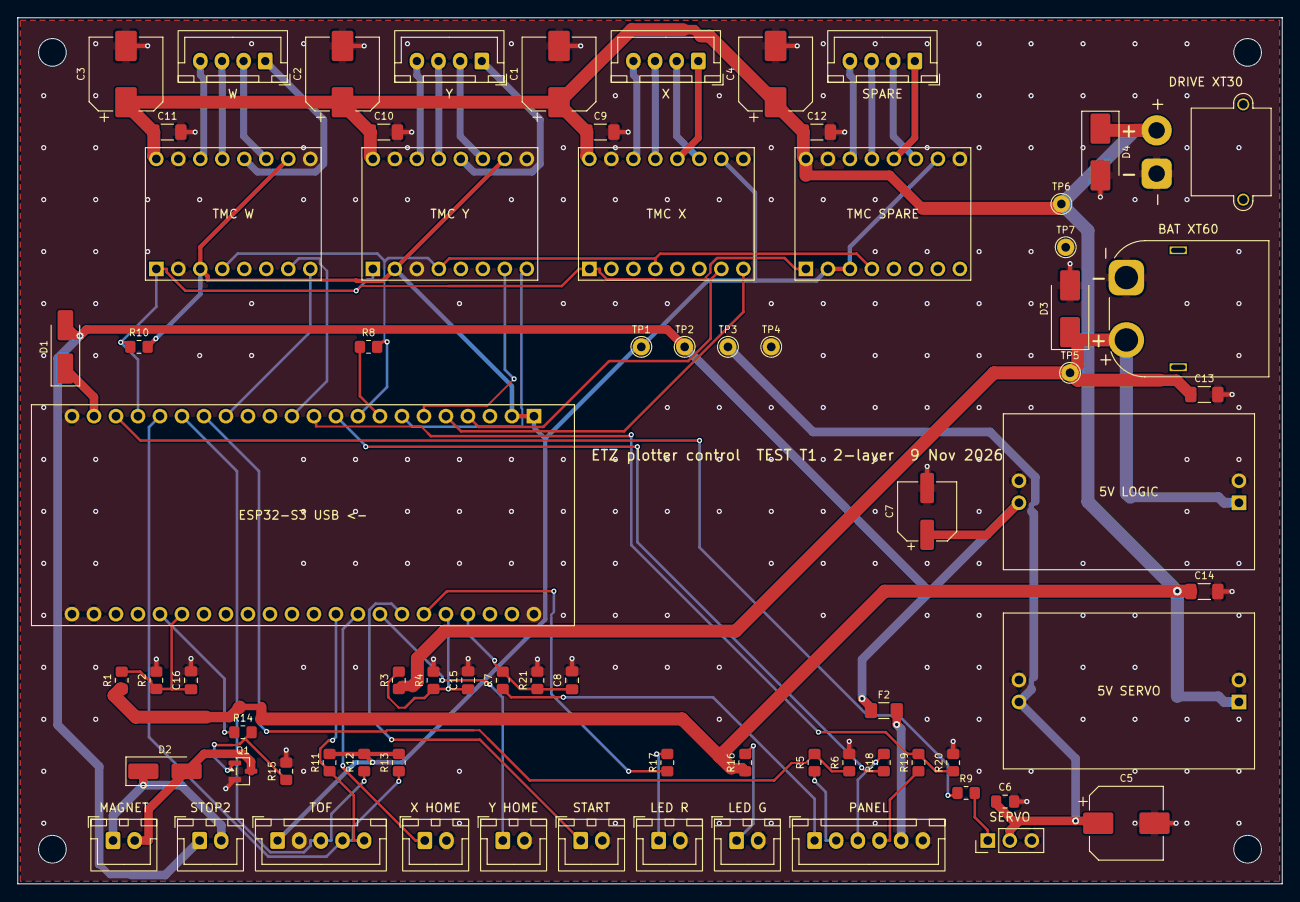
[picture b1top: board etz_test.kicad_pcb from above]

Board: 2 copper layers, 146.0 x 100.0 mm, 77 parts (0 on the bottom side), 58 nets.

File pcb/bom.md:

# Main control PCB: parts list (v1.0, 22 Oct 2026)

Source: `wiring.md` (power tree, ESP32-S3 pin map). One 2-layer board in place of the perfboard (`perfboard_100x80` in the model,
100 x 80 mm on 4 M3 standoffs). Modules plug into female headers, so a burnt module is a 1-minute swap.
Ask the organisers first that a self-designed board with plug-in driver modules counts as "own control electronics" (open item).

## Power tree
```
4S LiPo (XT60) -- F1 5 A blade fuse (inline) --+-- J_BAT (unswitched) --+-- U5 Mini560 Pro 5 V  -> +5V LOGIC
                                               |                        '-- R 100k / 15k -> GPIO2 (battery voltage)
                                               '-- stop block 1 (NC) -- J_DRIVE (switched) --+-- TMC2209 x4 VM (C 100 uF each)
                                                                                             +-- U6 Mini560 Pro 5 V -> +5V SERVO
                                                                                             +-- green LED (1.5 k)
                                                                                             '-- R 100k / 22k -> GPIO47 (stop sense)
+5V LOGIC -- D1 1N5819 -> ESP32 board 5V pin;  -> F2 PTC 0.5 A -> connector C V;  -> stop block 2 (NC) -> magnet 5 V
```

## A. Plug-in modules (on the PCB, on headers)
| Ref | Part | Qty | Footprint on the PCB | Notes |
|---|---|---|---|---|
| U1 | ESP32-S3-DevKitC-1 N16R8 | 1 | 2x 1x22 female headers, rows 25.4 mm apart (VERIFY) | USB-UART port = laptop link |
| U2..U4 | TMC2209 V1.3 (BIGTREETECH) | 3 | 2x 1x8 female headers each, rows 12.7 apart | X, Y, wrist |
| U7 | TMC2209 V1.3, spare | 1 | same | hot spare (its socket can stay empty) |
| U5 | **Mini560 Pro, 5 V version** | 1 | 4 pads: IN+ IN- OUT+ OUT- (VERIFY on your module), about 29 x 18 x 5.4 | 5 V logic: ESP32, magnet, connector C. Input 7..32 V (5 V version), up to 5 A |
| U6 | **Mini560 Pro, 5 V version** | 1 | same | servo rail. The Mini560 has no 6 V version (3.3 / 5 / 9 / 12 V); **never use the 9 V one on the MG996R** (max 7.2 V). At 5 V the lift uses about 25 % of the servo's stall torque: fine |

**No level shifter (22 Oct):** connector C uses R18 (1 k, TX) and R19 / R20 (10 k / 20 k divider, RX) instead of a BSS138 module.

## B. Small parts on the PCB
| Ref | Part | Qty | What for |
|---|---|---|---|
| Q1 | IRLZ44N logic-level N-MOSFET, TO-220 (home board; AO3400A SOT-23 on the factory board) | 1 | switches the magnet from GPIO21 |
| D1 | SS34 Schottky (SMA) | 1 | +5V LOGIC -> ESP32 board 5V pin (stops back-feeding the laptop's USB) |
| D2 | SS34 Schottky (SMA) | 1 | flyback across the magnet coil |
| F2 | PTC resettable fuse 0.5 A, 1206 | 1 | connector C V pin: a short on an external device cannot pull down the logic rail |
| C1..C4 | 100 uF 35 V SMD electrolytic, 8 x 10 | 4 | one at each TMC2209 VM pin |
| C5 | **470 uF 16 V SMD electrolytic, 8 x 10** | 1 | servo rail, at the servo connector: catches the MG996R's current spikes |
| C6 | **100 nF ceramic 1206** | 1 | servo rail, next to C5 (high-frequency noise) |
| C7 | 100 uF 10 V SMD electrolytic, 6.3 x 7.7 | 1 | +5V LOGIC, near the ESP32 (magnet switch-on spike) |
| C8 | 10 nF ceramic 1206 | 1 | connector A filter |
| R1 | 100 k | 1 | stop-sense divider (top) |
| R2 | 22 k | 1 | stop-sense divider (bottom) -> GPIO47 |
| R3 | 100 k | 1 | battery divider (top) |
| R4 | 15 k | 1 | battery divider (bottom) -> GPIO2 |
| R5 | 10 k | 1 | connector B divider (top) |
| R6 | 20 k | 1 | connector B divider (bottom) -> GPIO10 |
| R7, R21 | 10 k, 20 k | 2 | connector A divider (0..5 V -> 0..3.3 V) -> GPIO1 |
| R18 | 1 k | 1 | connector C TX (GPIO17) |
| R19, R20 | 10 k, 20 k | 2 | connector C RX divider -> GPIO18 |
| R8 | 1 k | 1 | TMC UART: GPIO15 TX -> PDN_UART bus |
| R9 | 1 k | 1 | servo PWM series (GPIO14) |
| R10 | 10 k | 1 | driver EN pull-up to 3V3 (drivers off while the ESP32 boots) |
| R11 | 10 k | 1 | distance sensor XSHUT pull-up |
| R12, R13 | 4.7 k | 2 | I2C pull-ups (fit only if the TOF400C has none) |
| R14 | 100 R | 1 | MOSFET gate |
| R15 | 100 k | 1 | MOSFET gate pull-down (magnet off while booting) |
| R16 | 1.5 k, 0.25 W | 1 | green LED on the drive bus (about 9 mA at 14.8 V) |
| R17 | 220 R | 1 | red LED from GPIO42 (about 6 mA) |
| TP1..TP4 | test pads (2 mm, through-hole) | 4 | 3V3, +5V LOGIC, +5V SERVO, GND (multimeter) |

Resistors and small capacitors 1206 (home board), hand-solder pads; they sit on the copper side.
TMC2209 addresses 0..3: MS1/MS2 tied to GND / 3V3 by traces (no parts).

## C. Connectors on the PCB
| Ref | Type | Pins | Goes to |
|---|---|---|---|
| J1..J3 | JST-XH 4-pin | 4 | X, Y, wrist steppers |
| J4 | JST-XH 4-pin (optional) | 4 | spare driver |
| J5 | 1x3 male pin header 2.54 | 3 | MG996R servo (signal, +5V SERVO, GND) |
| J6 | JST-XH 2-pin | 2 | magnet |
| J7, J8 | JST-XH 2-pin | 2 | X home switch, Y home switch |
| J9 | JST-XH 5-pin | 5 | distance sensor: 3V3, GND, SDA, SCL, XSHUT |
| J10 | XT60PW-M (PCB, horizontal) | 2 | battery in (after F1, before the stop) |
| J11 | XT30PW-M (PCB, horizontal) | 2 | drive bus in (after stop block 1) |
| J12 | JST-XH 2-pin | 2 | stop block 2: pin 1 +5V LOGIC out, pin 2 magnet 5 V back |
| J14 | JST-XH 2-pin | 2 | green LED |
| J15 | JST-XH 2-pin | 2 | red LED |
| J16 | JST-XH 2-pin | 2 | start button |
| J17 | JST-XH 6-pin | 6 | panel cable: A_SIG, B_SIG, C_TX, C_RX, +5 V (fused), GND; on the header strip V and GND are shared by A, B, C |

## D. Off the PCB (panel, cables, base)
| Part | Qty | Where |
|---|---|---|
| 4S LiPo 2200 mAh, XT60 | 1 | battery tray |
| XT60 + XT30 plugs (to match J10 / J11; check the genders) | 1 each | battery lead, stop button lead |
| F1: inline blade fuse holder + 5 A blade fuse (+ spares) | 1 | battery lead, before everything |
| Emergency stop 22 mm, latching, 2 NC blocks (XB2 / LAY37) | 1 | control panel |
| Start button 16 mm, momentary | 1 | control panel |
| LED 5 mm green + 5 mm red, with panel holders | 2 | control panel |
| Female headers 1x3, 1x3, 1x4 on a small strip board (connectors A, B, C) | 1 | control panel wall |
| 400-point breadboard | 1 | breadboard tray |
| JST-XH crimp housings + contacts kit (2/4/5/6-pin), Dupont 3-pin | 1 kit | harnesses |
| Silicone wire AWG16 (battery), AWG18 (drive bus), AWG24/26 (signals), 4-core AWG24 (steppers) | | harnesses |
| M3 standoffs 10 mm + screws | 4 | under the PCB (as now) |

## Open / VERIFY
- Mini560 Pro pad layout and exact size: send a photo of yours (top and bottom), or its listing.
- ESP32 DevKitC header row spacing.
- Whether the TOF400C has its own I2C pull-ups.
- Organisers: self-designed PCB allowed? Connector A/B V pin voltage (full rules text).
